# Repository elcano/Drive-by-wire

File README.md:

# DriveByWire

Obsolete. New code is in DBW version 5.

This repository is for use with the **Drive by Wire** board created to be used for the ELCANO self-driving tricycle. In order for this module to run external libraries are required.

Repositories were updated 6/8/2023 but clobbered previous history. Chief addition is use of an RC controller that allows manual control of throttle, brakes and steering.
The Sender files are intended for use on the Hi-Level board and do not really belong in the Drive-by-wire repository.

Libraries needed are listed below:

ALL Versions ________________________________
* PID by Brett Beauregard
    https://github.com/br3ttb/Arduino-PID-Library
    A simple controller calculator (proportional integral derivative) to calculate the error between a desired output and an actual output. Has files **PID_v1**

Version 3 (Arduino Mega) ________________________________
* CAN_BUS_SHIELD by Seeed-Studio
    https://github.com/Seeed-Studio/CAN_BUS_Shield
    Contains CAN_BUS communication protocols and required files such as **mcp_can** and **can-serial**

* Pin Change Interrupt by Nico Hood
    https://github.com/NicoHood/PinChangeInterrupt
    For custom configuration of Arduino pin properties. Has files **PinChangeInterupt**

* MCP48x2 DAC by Jonas Forsberg
    https://github.com/SweBarre/MCP48x2.
    Library for Digital to anolog converter. Has files **MCP48x2**

Version 4 (Arduino Due)  _______________________________________________
* Due CAN and CAN Common by Collin Kidder
    https://github.com/collin80/due_can
    https://github.com/collin80/can_common

## To Install

* Download the **Drive_By_Wire** module into the project parent directory
```
git clone https://github.com/elcano/Drive-by-wire.git
```
* Move into the **Drive_By_Wire** folder
```
cd Drive_By_Wire
```
* Download the required libraries
```
git clone https://github.com/Seeed-Studio/Seeed_Arduino_CAN.git
git clone https://github.com/br3ttb/Arduino-PID-Library.git
git clone https://github.com/NicoHood/PinChangeInterrupt.git
git clone https://github.com/SweBarre/MCP48x2.git
git clone https://github.com/ivanseidel/DueTimer.git
git clone https://github.com/collin80/can_common.git
git clone https://github.com/collin80/due_can.git
```
* Add the folders above to the IDE directory. In Windows, add the required libraries to: C:\Users\<username>\Documents\Arduino\libraries
* Arduino Due requires additional installation. On the IDE, go to Tools -> Boards -> Boards Manager -> Arduino SAM Boards (32-bits ARM Cortex-M3) 

## Navigating Arduino IDE: 
* **Selecting Board:** Tools -> Board -> Arduino AVR/SAM Boards -> Arduino Mega/Due
* **Selecting Serial Port:** Tools -> Port -> COM (Arduino Mega/Due)
* **Accessing Serial Monitor:** Right-hand Corner -> Select Baud Rate (115200)

## Drive-by-Wire: 
* **Low-level board code with RC control support with existing code for brakes, steering, and throttle.** 

## Test: 
* **Low-level board code with three functions to test each subsystems individually (brakes, steering, throttle).** 
* testBrake(): Activates brakes with 24V via Stop(), Holds brakes with 12V after 800ms via Update(), Releases brakes every ~2 seconds.
* testThrottle(): Gradually increases speed and decreases speed on DACA.
* testSteering(): Changes directions every 3 seconds, moving the linear actuator. 

## Sender: 
* **High-level board code to communicate with low-level board using CAN communication.** 
* Arguments for Function: Each data is reserved for 2 bytes. 
    *   currentSpeed: Controls the speed via the DACA, input: (0 -255).
    *   currentBrake: Apply and updates brakes if necessary, input: (0 - releases brakes, anything above 0 - applies brakes).
    *   currentAngle: Changes direction based on input (may need to calibrate based on sensors), left: 779 (1ms), middle: 722 (1.5ms), right: 639 (1.85ms).

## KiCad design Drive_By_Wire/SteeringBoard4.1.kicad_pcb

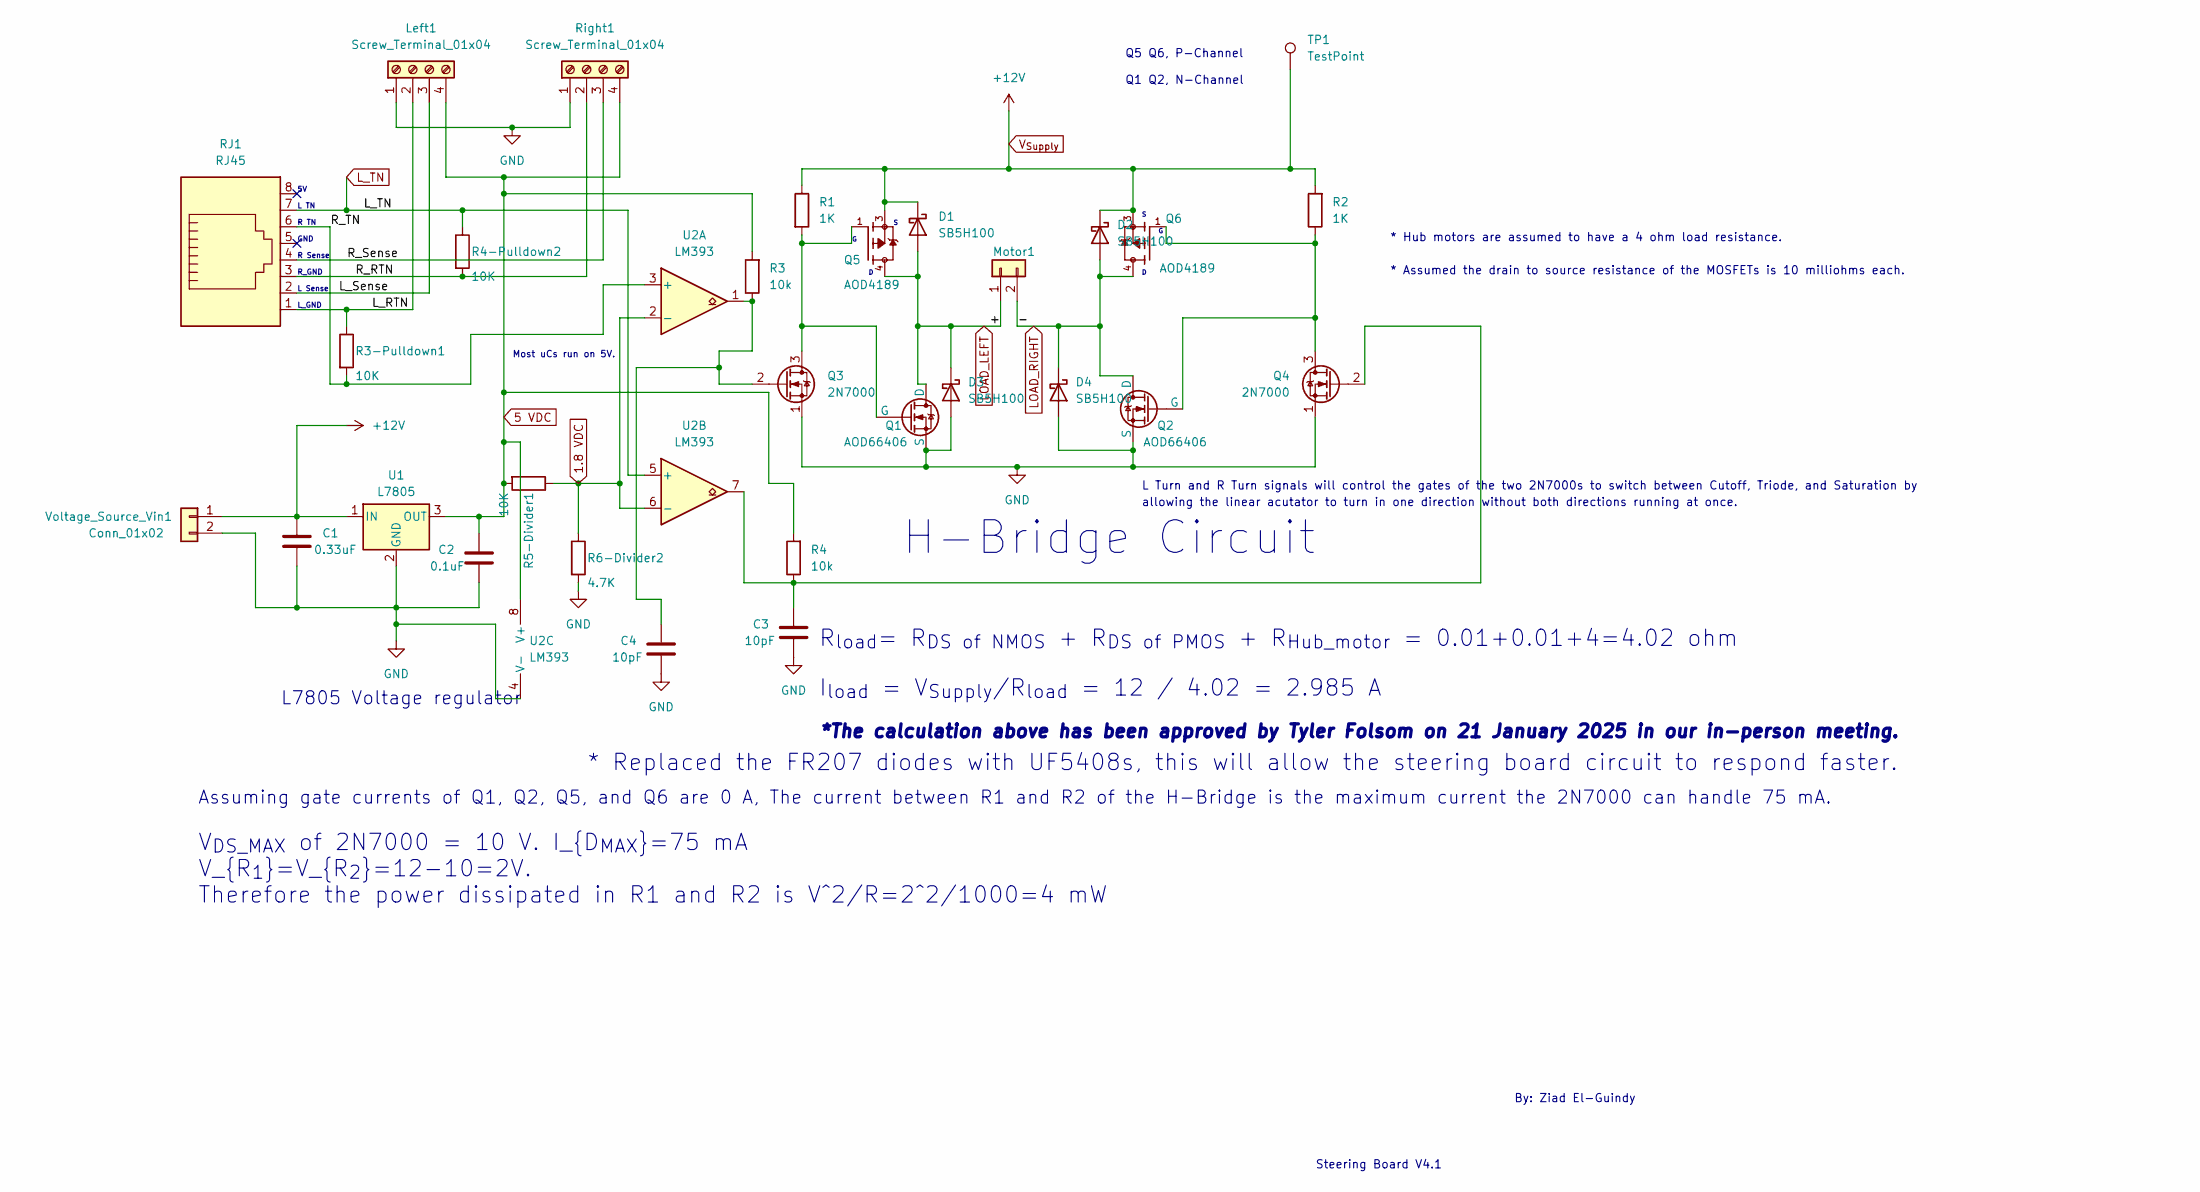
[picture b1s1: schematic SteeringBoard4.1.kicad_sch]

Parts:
C1: 0.33uF; C_Radial_D5.0mm_H7.0mm_P2.00mm
C2: 0.1uF; C_Radial_D5.0mm_H7.0mm_P2.00mm
C3, C4: 10pF; C_Radial_D5.0mm_H7.0mm_P2.00mm
D1, D2, D3, D4: SB5H100; D_DO-201AD_P15.24mm_Horizontal
Left1: Screw_Terminal_01x04; TerminalBlock_MetzConnect_Type059_RT06304HBWC_1x04_P3.50mm_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
Motor1: Conn_01x02; Anderson_Conn
Q1, Q2: AOD66406
Q3, Q4: 2N7000; TO-92_Inline
Q5, Q6: AOD4189; DPACK
R1, R2: 1K; R_Axial_DIN0414_L11.9mm_D4.5mm_P15.24mm_Horizontal
R3, R4: 10k; R_Axial_DIN0204_L3.6mm_D1.6mm_P5.08mm_Horizontal
R3-Pulldown1, R4-Pulldown2, R5-Divider1: 10K; R_Axial_DIN0204_L3.6mm_D1.6mm_P5.08mm_Horizontal
R6-Divider2: 4.7K; R_Axial_DIN0204_L3.6mm_D1.6mm_P5.08mm_Horizontal
RJ1: RJ45; RJ45_Amphenol_54602-x08_Horizontal
Right1: Screw_Terminal_01x04; TerminalBlock_MetzConnect_Type059_RT06304HBWC_1x04_P3.50mm_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
TP1: TestPoint; Pin_D1.0mm_L10.0mm
U1: L7805; TO-220-3_Vertical
U2: LM393; DIP-8_W7.62mm
Voltage_Source_Vin1: Conn_01x02; Anderson_Conn

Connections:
1.8 VDC: R5-Divider1.1, R6-Divider2.1, U2.2 (-), U2.6 (-)
5 VDC: C2.1, Left1.4, R3.2, R4.2, R5-Divider1.2, Right1.4, U1.3 (OUT), U2.8 (V+)
/L_RTN: Left1.2, R3-Pulldown1.1, RJ1.1
/L_Sense: Left1.3, RJ1.2
/R_RTN: R4-Pulldown2.2, RJ1.3, Right1.2
/R_Sense: RJ1.4, Right1.3
/R_TN: R3-Pulldown1.2, RJ1.6, U2.3 (+)
GND: C1.2, C2.2, C3.2, C4.2, D3.2 (A), D4.2 (A), Left1.1, Q1.3 (S), Q2.3 (S), Q3.1 (S), Q4.1 (S), R6-Divider2.2, Right1.1, U1.2 (GND), U2.4 (V-), Voltage_Source_Vin1.2
LOAD_LEFT: D1.2 (A), D3.1 (K), Motor1.1, Q1.1 (D), Q5.4
LOAD_RIGHT: D2.2 (A), D4.1 (K), Motor1.2, Q2.1 (D), Q6.4
L_TN: R4-Pulldown2.1, RJ1.7, U2.5 (+)
unnamed: Q1.2 (G), Q3.3 (D), Q5.1, R1.2
unnamed: Q2.2 (G), Q4.3 (D), Q6.1, R2.1
unnamed: C4.1, Q3.2 (G), R3.1, U2.1
unnamed: C3.1, Q4.2 (G), R4.1, U2.7
V_{Supply}: C1.1, D1.1 (K), D2.1 (K), Q5.3, Q6.3, R1.1, R2.2, TP1.1, U1.1 (IN), Voltage_Source_Vin1.1

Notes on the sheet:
R Sense
R TN
GND
V_{DS_MAX} of 2N7000 = 10 V. I_{D_{MAX}}=75 mA V_{R_{1}}=V_{R_{2}}=12-10=2V. Therefore the power dissipated in R1 and R2 is V^2/R=2^2/1000=4 mW
Steering Board V4.1
R_{load}= R_{DS of NMOS} + R_{DS of PMOS} + R_{Hub_motor} = 0.01+0.01+4=4.02 ohm
* Assumed the drain to source resistance of the MOSFETs is 10 milliohms each.
I_{load} = V_{Supply}/R_{load} = 12 / 4.02 = 2.985 A
Assuming gate currents of Q1, Q2, Q5, and Q6 are 0 A, The current between R1 and R2 of the H-Bridge is the maximum current the 2N7000 can handle 75 mA.
* Hub motors are assumed to have a 4 ohm load resistance.
* Replaced the FR207 diodes with UF5408s, this will allow the steering board circuit to respond faster.
allowing the linear acutator to turn in one direction without both directions running at once.
L TN
L Turn and R Turn signals will control the gates of the two 2N7000s to switch between Cutoff, Triode, and Saturation by
H-Bridge Circuit
Most uCs run on 5V.
*The calculation above has been approved by Tyler Folsom on 21 January 2025 in our in-person meeting.
L_GND
L Sense
Q5 Q6, P-Channel Q1 Q2, N-Channel
By: Ziad El-Guindy
R_GND
L7805 Voltage regulator

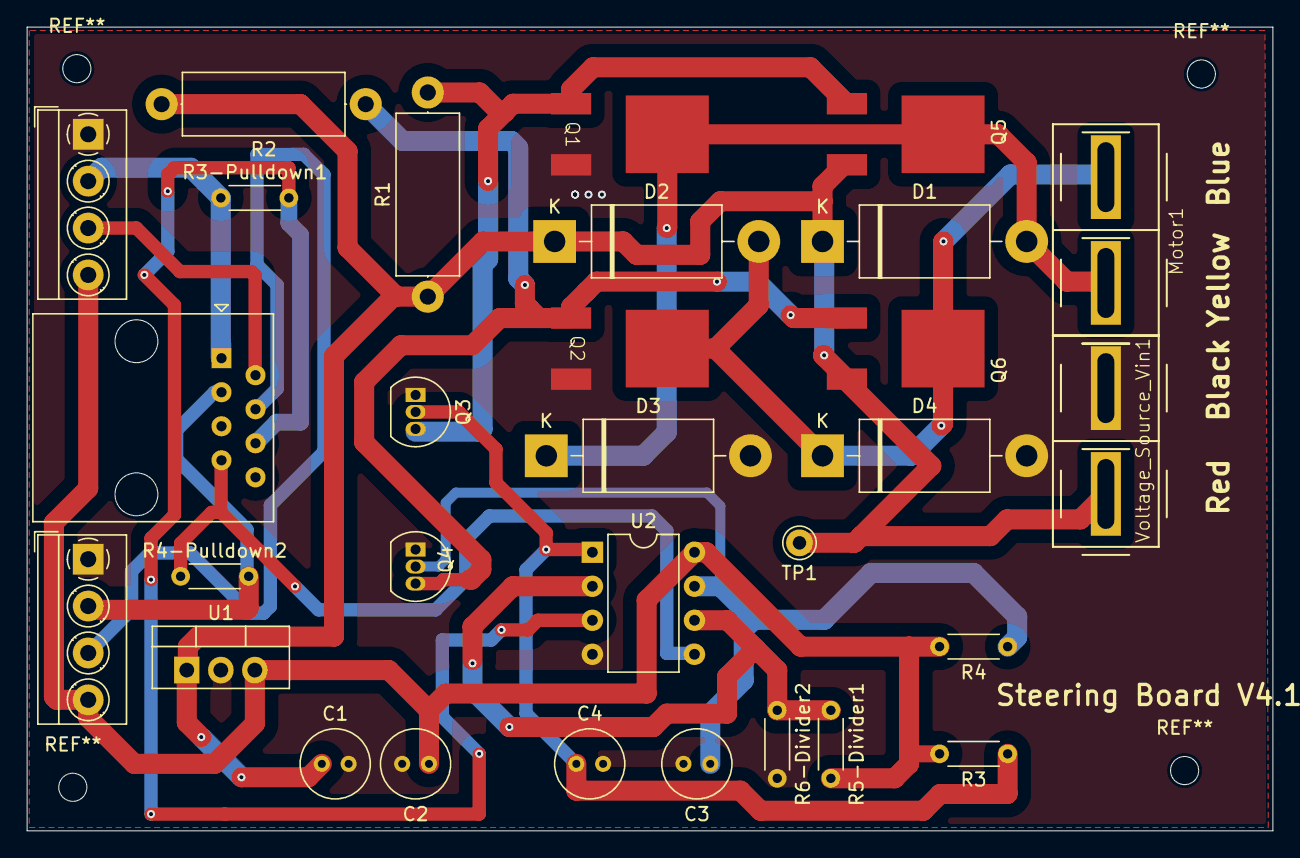
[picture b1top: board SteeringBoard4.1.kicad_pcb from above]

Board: 2 copper layers, 93.0 x 60.0 mm, 30 parts (0 on the bottom side), 16 nets.

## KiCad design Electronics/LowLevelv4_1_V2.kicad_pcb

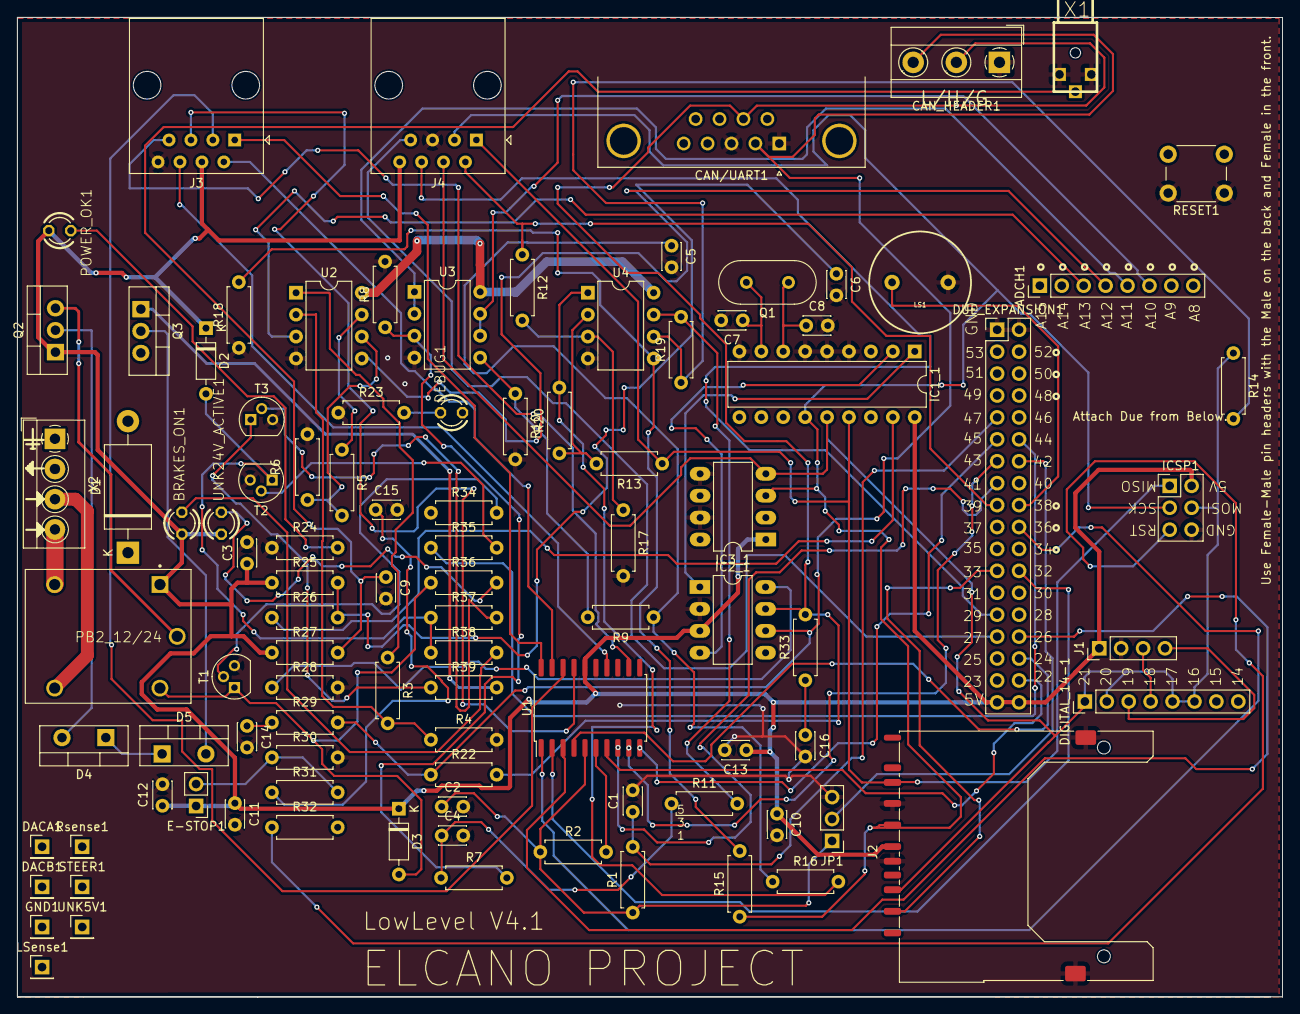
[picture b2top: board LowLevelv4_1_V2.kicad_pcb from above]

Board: 2 copper layers, 146.6 x 113.5 mm, 100 parts (0 on the bottom side), 80 nets.

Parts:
ADCH1: Analog In 8-11, DAC, CAN; PinHeader_1x08_P2.54mm_Vertical
BRAKES_ON1: LED3MM
C1, C9, C15: 1uF; C_Disc_D3.0mm_W2.0mm_P2.50mm
C2, C3, C4, C5, C6, C10, C11, C12, C13: 0.1uF; C_Disc_D3.0mm_W2.0mm_P2.50mm
C7, C8: 33pF; C_Disc_D3.0mm_W2.0mm_P2.50mm
C14, C16: 560pF; C_Disc_D3.0mm_W2.0mm_P2.50mm
CAN/UART1: DB9 Plug; DSUB-9_Male_Horizontal_P2.77x2.84mm_EdgePinOffset4.94mm_Hou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
CAN_HEADER1: CONN_03-SCREW-5MM; TerminalBlock_MetzConnect_Type055_RT01503HDWU_1x03_P5.00mm_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
D1: 1N5400; D_DO-201_P15.24mm_Horizontal
D2, D3: 1N4148; D_DO-35_SOD27_P7.62mm_Horizontal
D4, D5: MBR745; TO-220-2_Vertical
DACA1: PTR1PAD1-17; PinHeader_1x01_P2.54mm_Vertical
DACB1: PTR1PAD1-17; PinHeader_1x01_P2.54mm_Vertical
DEBUG1: LED3MM
DIGITAL_14-1: Digital 14-21; PinHeader_1x08_P2.54mm_Vertical
DUE_EXPANSION1: Digital 22-53; PinHeader_2x18_P2.54mm_Vertical
E-STOP1: PINHD-1X2; PinHeader_1x02_P2.54mm_Vertical
GND1: PTR1PAD1-17; PinHeader_1x01_P2.54mm_Vertical
IC1_1: MCP2515(MCP2510)P; DIP-18_W7.62mm
IC2_1: MCP2551DIL08; DIP-8_W7.62mm_LongPads
IC3_1: MCP4802; DIP-8_W7.62mm_LongPads
ICSP1: 2x3; PinHeader_2x03_P2.54mm_Vertical
J1: ROS_CONN; PinHeader_1x04_P2.54mm_Vertical
J2: SD_Card; SD_Kyocera_145638109511859+
J3: RJ45_MOTOR; RJ45_Amphenol_54602-x08_Horizontal
J4: RJ45_STEER; RJ45_Amphenol_54602-x08_Horizontal
JP1: Jumper_3_Open; PinHeader_1x03_P2.54mm_Vertical
LS1: BUZZER-PTH; BUZZER-12MM
LSense1: PTR1PAD1-17; PinHeader_1x01_P2.54mm_Vertical
PB2_12/24: ORWH-SH-105D1F,000; TE_ORWH-SH-105D1F,000
POWER_OK1: LED3MM
Q1: ECS-160-20-46X; Crystal_HC49-U_Vertical
Q2, Q3: IRLZ44N; TO-220-3_Vertical
R1, R11, R16: 4.7k; R_Axial_DIN0207_L6.3mm_D2.5mm_P7.62mm_Horizontal
R2, R4, R8, R30, R31: 10k; R_Axial_DIN0207_L6.3mm_D2.5mm_P7.62mm_Horizontal
R3, R5, R6, R7, R9, R10: 5.15k; R_Axial_DIN0207_L6.3mm_D2.5mm_P7.62mm_Horizontal
R12, R13, R14, R15, R17, R18, R19, R20: 22k; R_Axial_DIN0207_L6.3mm_D2.5mm_P7.62mm_Horizontal
R22: 120; R_Axial_DIN0207_L6.3mm_D2.5mm_P7.62mm_Horizontal
R23, R24, R26, R34, R35, R36, R38: 1K; R_Axial_DIN0207_L6.3mm_D2.5mm_P7.62mm_Horizontal
R25: 20K; R_Axial_DIN0207_L6.3mm_D2.5mm_P7.62mm_Horizontal
R27, R28: 4.7K; R_Axial_DIN0207_L6.3mm_D2.5mm_P7.62mm_Horizontal
R29, R33, R39: 100; R_Axial_DIN0207_L6.3mm_D2.5mm_P7.62mm_Horizontal
R32: 0; R_Axial_DIN0207_L6.3mm_D2.5mm_P7.62mm_Horizontal
R37: 1k; R_Axial_DIN0207_L6.3mm_D2.5mm_P7.62mm_Horizontal
RESET1: MOMENTARY-SWITCH-SPST-PTH-6.0MM; SW_PUSH_6mm
Rsense1: PTR1PAD1-17; PinHeader_1x01_P2.54mm_Vertical
STEER1: PTR1PAD1-17; PinHeader_1x01_P2.54mm_Vertical
T1, T2, T3: 2N3904; TO-92
U1: TXB0108DQSR; SOIC-20W_7.5x12.8mm_P1.27mm
U2, U3, U4: LM358; DIP-8_W7.62mm
UNK5V1: PTR1PAD1-17; PinHeader_1x01_P2.54mm_Vertical
UNK24V_ACTIVE1: LED3MM
X1: ODO_JACK
X2: TerminalBlock_4Ucon_1x04_P3.50mm_Horizontal

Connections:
+3.3V: C2.1, JP1.1 (A), R1.1, R2.1, U1.5 (VCCA)
+5V: BRAKES_ON1.A, C3.1, C10.1, C11.1, C12.1, C13.1, D2.1 (K), D3.1 (K), DUE_EXPANSION1.35, DUE_EXPANSION1.36, E-STOP1.1, IC1_1.18 (VDD), IC2_1.3 (VDD), IC3_1.1, ICSP1.2, J1.1 (5V), J2.4 (VDD), J3.4, J4.8, PB2_12/24.1 (C1), POWER_OK1.A, Q2.1 (G), R25.1, R27.1, U1.16 (VCCB), UNK24V_ACTIVE1.A
+12V: U2.8 (V+), U3.8 (V+), U4.8 (V+)
/Low Level 4.1 Segment 1/5V_DAC1: R3.1, U2.1
/Low Level 4.1 Segment 1/5V_FWDSW: J3.1, U1.20 (B1)
/Low Level 4.1 Segment 1/5V_REGEN: J3.6, U1.14 (B5)
/Low Level 4.1 Segment 1/5V_REVERSE: J3.5, U1.17 (B4)
/Low Level 4.1 Segment 1/5V_SPEEDOMETER: J3.7, U1.12 (B7)
/Low Level 4.1 Segment 1/5V_STEER_PULSE: J3.3, U1.18 (B3)
/Low Level 4.1 Segment 1/5V_THROTTLE: R5.1, U2.7
/Low Level 4.1 Segment 1/5V_WATCHDOG: J3.2, U1.19 (B2)
/Low Level 4.1 Segment 1/BRAKE_PULSE: DUE_EXPANSION1.15, U1.8 (A6)
/Low Level 4.1 Segment 1/CAN_ENABLE: DUE_EXPANSION1.14, JP1.2 (C)
/Low Level 4.1 Segment 1/CHIP_SELECT_ANGLE: DUE_EXPANSION1.17, J4.2, R12.1
/Low Level 4.1 Segment 1/CHIP_SELECT_SD: DUE_EXPANSION1.23, J2.1 (CD/DAT3)
/Low Level 4.1 Segment 1/DAC1: ADCH1.3, U2.3 (+)
/Low Level 4.1 Segment 1/EBIKE_POWER_IN: DUE_EXPANSION1.11, U1.10 (A8)
/Low Level 4.1 Segment 1/FWDSW: DUE_EXPANSION1.20, U1.1 (A1)
/Low Level 4.1 Segment 1/IRPT_WHEEL: C1.1, DUE_EXPANSION1.9, R1.2
/Low Level 4.1 Segment 1/REGEN: DUE_EXPANSION1.34, U1.7 (A5)
/Low Level 4.1 Segment 1/REVERSE: DUE_EXPANSION1.32, U1.4 (A4)
/Low Level 4.1 Segment 1/RX1_DBW: DIGITAL_14-1.3, J1.4 (RX1)
/Low Level 4.1 Segment 1/R_SENSE: ADCH1.5, U3.1, U3.2 (-)
/Low Level 4.1 Segment 1/SPEEDOMETER: DUE_EXPANSION1.13, U1.9 (A7)
/Low Level 4.1 Segment 1/STEER_PULSE/L_TURN: DUE_EXPANSION1.30, U1.3 (A3)
/Low Level 4.1 Segment 1/THROTTLE_DAC0: ADCH1.4, U2.5 (+)
/Low Level 4.1 Segment 1/TX1_DBW: DIGITAL_14-1.4, J1.3 (TX1)
/Low Level 4.1 Segment 1/WATCHDOG: DUE_EXPANSION1.24, U1.2 (A2)
/Low Level 4.1 Segment 2/CAN_RXD: IC1_1.2 (RXCAN), IC2_1.4 (RXD)
/Low Level 4.1 Segment 2/CAN_TXD: IC1_1.1 (TXCAN), IC2_1.1 (TXD)
/Low Level 4.1 Segment 2/OSC1: C7.1, IC1_1.8 (OSC1), Q1.2
/Low Level 4.1 Segment 2/OSC2: C8.1, IC1_1.7 (OSC2), Q1.1
/Low Level 4.1 Segment 2/RS: IC1_1.17 (RESET), R26.1
/Low Level 4.1 Segment 3/SOLENOID_OUT: D4.1 (K), D5.1 (K)
/Low Level 4.1 Segment 3/SOLENOID_POWER: PB2_12/24.3 (C), Q2.3 (S)
BRAKE_ON: DUE_EXPANSION1.12, R35.1
BUZZER: DUE_EXPANSION1.18, LS1.+ (1)
CANH: CAN/UART1.7, CAN_HEADER1.2, IC2_1.7 (CANH), R22.2, R33.2
CANL: CAN/UART1.2, CAN_HEADER1.3, IC2_1.6 (CANL), R22.1, R29.2
ESTOP_INT: C15.1, R31.1
GND: C1.2, C2.2, C3.2, C4.2, C5.2, C6.2, C7.2, C8.2, C9.2, C10.2, C11.2, C12.2, C13.2, C14.2, C15.2, C16.2, CAN/UART1.1, CAN/UART1.3, CAN_HEADER1.1, DUE_EXPANSION1.1, DUE_EXPANSION1.2, IC1_1.4 (TX0RTS), IC1_1.5 (TX1RTS), IC1_1.6 (TX2RTS), IC1_1.9 (VSS), IC2_1.2 (VSS), IC3_1.5, IC3_1.7, ICSP1.6, J1.2 (GND), J2.3 (VSS), J2.6 (VSS), J2.12 (SHELL1), J2.13 (SHELL2), J3.8, J4.5, JP1.3 (B), LS1.- (2), R4.2, R6.2, R8.2, R10.2, R17.2, R18.1, R23.1, R24.1, R28.2, R30.2, RESET1.1, T1.3 (E), T2.3 (E), T3.3 (E), U1.15 (GND), U2.4 (V-), U3.4 (V-), U4.4 (V-), X1.P$2 (2), X1.P$3 (3)
L_SENSE: ADCH1.6, U3.6 (-), U3.7
L_TN: DUE_EXPANSION1.29, J4.7
MISO: IC1_1.15 (SO), ICSP1.1, J2.7 (DAT0), J4.1, R13.1
MOSI: DIGITAL_14-1.1, DIGITAL_14-1.2, DIGITAL_14-1.5, DIGITAL_14-1.6, IC1_1.14 (SI), IC3_1.4, ICSP1.4, J2.2 (CMD), J4.4, R14.1
unnamed: BRAKES_ON1.K (C), R38.2
unnamed: C4.1, R7.1, R11.1
unnamed: C5.1, R9.1, R16.1
unnamed: C6.1, R25.2, R26.2
unnamed: C14.1, R29.1
unnamed: C16.1, R33.1
unnamed: D2.2 (A), R37.1, R38.1, T2.1 (C)
unnamed: D3.2 (A), PB2_12/24.2 (C2), R36.1, T1.1 (C)
unnamed: D4.2 (A), Q2.2 (D)
unnamed: D5.2 (A), Q3.2 (D)
unnamed: DEBUG1.K (C), R23.2
unnamed: E-STOP1.2, R30.1, R31.2
unnamed: IC2_1.8 (RS), R28.1
unnamed: POWER_OK1.K (C), R24.2
unnamed: Q3.1 (G), R39.2
unnamed: R11.2, R19.2, U4.7
unnamed: R16.2, R20.2, U4.1
unnamed: R34.2, T1.2 (B)
unnamed: R35.2, T2.2 (B)
unnamed: R37.2, T3.2 (B)
unnamed: R39.1, T3.1 (C)
unnamed: R2.2, U1.6 (OE)
unnamed: R3.2, R4.1, U2.2 (-)
unnamed: R5.2, R6.1, U2.6 (-)
unnamed: R7.2, R8.1, U3.3 (+)
unnamed: R9.2, R10.1, U3.5 (+)
unnamed: R12.2, R17.1, U4.3 (+)
unnamed: R13.2, R20.1, U4.2 (-)
unnamed: R15.2, R18.2, U4.5 (+)
unnamed: R14.2, R19.1, U4.6 (-)
unnamed: R36.2, UNK24V_ACTIVE1.K (C)
RESET: ICSP1.5, R32.1
R_TN: DUE_EXPANSION1.27, J4.6
SCK: IC1_1.13 (SCK), IC3_1.3, ICSP1.3, J2.5 (CLK), J4.3, R15.1
WHEELROTATION: C9.1, R27.2, X1.P$1 (1)

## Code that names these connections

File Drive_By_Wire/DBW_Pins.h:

#ifndef _DBW_PINS_
#define _DBW_PINS_

#define DEBUG false
#define USE_PIDS false // throttle currently uses a PID controller, Steering does not current use a PID controller

#include <Arduino.h>

//Version can be 1,3 or 4; LLB = Low Level Board = Drive By Wire
#define DBWversion 4

/*---------- Version 1 - No Longer supported------------------------
#if DBWversion == 1
//Wheel click interrupt
#define IRPT_WHEEL         3
#define STEER_OUT_PIN      5
#define STEER_ON           8
#define BrakeVoltPin       9
#define BrakeOnPin        10
#define SelectAB          53
#define SelectCD          49
#define DAC_CHANNEL        0
#define AngleSensorLeft   A2
#define AngleSensorRight  A3
*/
/*---------- Version 3: Arduino Mega -------------------------------------*/
#if DBWversion < 4

/* Pin declarations */
// Serial Monitor uses pins 0,1 for RX0,TX0
// Servo to control the brakes; not used

#define BRAKE_PULSE_PIN     2
 // keep-alive watchdog is not yet implemented
#define WATCHDOG_PIN        5  
// Pin used to steer the vehicle with a pulse
#define STEER_PULSE_PIN     6
// Relay that turns on power to the steering system
#define STEER_ON_PIN        8
// Wheel angle sensors mounted on left and right steering columns
#define L_SENSE_PIN    A2
#define R_SENSE_PIN    A3

// Command to e-bike controller to use regenerative braking; not used 
#define REGEN_PIN          22
// Command to e-bike controller to drive in reverse; not used
#define REVERSE_PIN        24
// Switch to drive in forward or reverse; not used
#define FWDSW_PIN          34
#define D_36_PIN           36  // Not used
// Brakes, have relays for both on/off as well as selecting 12/24v power.
#define BrakeVoltPin       37
#define BUZZER_PIN         38  // Not used
#define BrakeOnPin         39

// CANbus slave select
#define CAN_SS_PIN         49  
// SPI chip select for DAC slave select. Channel A is for throttle
#define DAC_SS_PIN         48 
// we only use channel A for the throttle. B is routed but unused.
#define DAC_CHANNEL         0   
// Pins 51,52,53 are MISO, MOSI, SCK.
// originally intended as a return ground, these analog pins are free and on the steering header.
// Intent was to use L_SENSE - L_RTN as a differential signal.
//#define L_RTN_PIN        A6
//#define R_RTN_PIN        A7

/* Signals A8 through A15 are digital interrupts */
/* The Arduino Mega only has 6 interrupts, but an additional 8 can be added through the port pin change interrupt. */
//Wheel click interrupt (digitally high or low, referred to as an "odometer"). Once per wheel revolution.
// IRPT_WHEEL = WHEELROTATION
#define IRPT_WHEEL         A8
// physical E-Stop port; not used
#define IRPT_ESTOP_PIN     A9 
// Interrupt for can msg; not used
#define IRPT_CAN_PIN       A10 

// motor hall phases occur multiple times per wheel revolution
// A future design may make use of these for more precise speed feedback.
// The speedometer_pin would be jumpered to the signal in use
//Not implemented
#define SPEEDOMETER_PIN    A11
#define IRPT_PHASE_C       A12
#define EBIKE_POWER_IN_PIN A13
#define IRPT_PHASE_B       A14
#define IRPT_PHASE_A       A15


/*---------- Version 4: Arduino Due -------------------------------------*/
#else // DBWversion >=4

// Serial Monitor uses pins 0,1 for RX0,TX0
// Pins D0-D13 and A0-A5 are reserved for the Motor Shield
// The shield may block access to A6 and A7.
/*
 *  --------Motor shield pins --------------
 *  Channel A Current sensing   A0
 *  Channel B Current sensing   A1
 *  In2 Connector               A2
 *  In3 Connector               A3
 *  Channel A Speed (PWM)       3
 *  Out5 connector              5
 *  Out6 connector              6
 *  Channel B Brake             8
 *  Channel A Brake             9
 *  Channel B Speed (PWM)       11
 *  Channel A Direection        12
 *  Channel B Direection        13
 *  
 *  Version 4 connectors:
 *  RJ45 Steering: 
 *        L_RTN, L_SENSE, GND, 5V, STEER_PULSE, GND, R_RTN, R_SENSE, GND, 5V
 *  Two 4 wire screw terminals for CAN bus
 *        12V in, GND, CAN LO, CAN HI
 *  One 4 wire screw terminal for brake solenoid
 *        12V in, GND, 24V in, Brake solenoid out (12 or 24V)
 *        The 12V in on this connector is tied to the 12V in on the CAN bus connector,
 *        There should be only one connector to 12V power in, 
 *        A spare 12V connector could be wired to the motor shield, which
 *        already has a common ground.`
 *  One 4 wire screw terminal:
 *        12V out (controlled by STEER_ON), GND, IRPT_WHEEL, GND
 *  RJ45 to e-bike Motor Controller:
 *        FWDSW, EBIKE_POWER_IN, GND, DAC0, DAC1, SPEEDOMETER, WATCHDOG, 
 *        BRAKE_PULSE, REVERSE, REGEN, 

 */

// Wheel angles sensors mounted on left and right steering columns
#define L_SENSE_PIN        A10
#define R_SENSE_PIN        A11
// originally intended as a return ground, these analog pins are free and on the steering header.
// Intent was to use L_SENSE - L_RTN as a differential signal.
//#define L_RTN_PIN          26
//#define R_RTN_PIN          27

//----NEWLY ADDED PINs 6/8/25-----
#define THROTTLE_BR_CH2_PIN 9
#define STEERING_CH1_PIN 8

#define DRIVE_MODE_CH4_PIN 11
#define RC_CH3_ESTOP 10
#define RIGHT_TURN_PIN 29
#define LEFT_TURN_PIN 27

// Command to e-bike controller to use regenerative braking; not used 
#define REGEN_PIN           22
// The odd numbered pins from 23 to 39 are unassigned.

// Command to e-bike controller to drive in reverse; not used
#define REVERSE_PIN         24
// Pin used to steer the vehicle with a pulse
#define STEER_PULSE_PIN     26
// Relay that turns on power to the steering system
#define STEER_ON_PIN        4
// Debug or status for DBW
#define DBW_LED             30
 // keep-alive watchdog is not yet implemented
#define WATCHDOG_PIN        32  
// Pins 34 and 35 could conflict with the Router board on the Bridge.
// Switch to drive in forward or reverse; not used
#define FWDSW_PIN          36
#define BUZZER_PIN         38  // Not used
#define BrakeOnPin         39
// Brakes, have relays for both on/off as well as selecting 12/24v power.
#define BrakeVoltPin       40

// Servo to control the brakes; not used
#define BRAKE_PULSE_PIN    41
/* Signals D42-49 are digital interrupts */
/* If implemented on aa Arduino Mega, these are on Port L and can use pin change interrupt. */
/* Any Arduino Due pin can be an interrupt. */
// Interrupt for can msg; not used
#define IRPT_CAN_PIN       42
// Multiple clicks per wheel revolution (not implemented)
#define SPEEDOMETER_PIN    43
// When the E-bike controller has power, this line is 5V.
// If it falls to zero, ebike has lost power.
#define EBIKE_POWER_IN_PIN 45

// Wheel click interrupt (digitally high or low, referred to as an "odometer"). Once per wheel revolution.
// Odometer reed switch is pulled up to high voltage.
// IRPT_WHEEL = WHEELROTATION
#define IRPT_WHEEL         47
// DAC channel is he DAC address for throttle; not an Arduino pin.
#define DAC_CHANNEL         0   
/*------------ Dropped signals ------------------
 * The following signals have been dropped
// Motor hall phases occur multiple times per wheel revolution
// A future design may make use of these for more precise speed feedback.
// The speedometer_pin would be jumpered to the signal in use
   The three Hall Phases were never used: IRPT_PHASE_A, IRPT_PHASE_B, IRPT_PHASE_C
   If we use a signal from the hub motor, it will be on the SPEEDOMETER_PIN 

// physical E-Stop port; not used
  IRPT_ESTOP_PIN is not used. It was intended for a remote e-stop, but the
  e-stop now comes from the CAN bus.
  D_36_PIN    // Never used; intended as a spare signal
 -------------------------------------------------------------*/

// On the Due, SPI, CAN_SS and DAC_SS are not used. Use DAC0, DAC1, CANRX and CANTX  
// On Due MISO, MOSI, SCK are only on the ICSP, which is blocked by the motor shield.

#endif  // DBWversion 

#endif   //_DBW_PINS_

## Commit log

2019-12-04 Rename Elcano_C2_LowLevel_TimedBrakes.ino to TimedBrakes.ino
2019-12-04 Rename Elcano_C2_LowLevel.ino to Drive_ByWire.ino
2019-12-04 Rename Drive_ByWire.ino to Drive_By_Wire.ino
2020-04-24 just a test comment
2020-04-24 comment
2020-05-12 Moving library files to compile --> TODO: Consolidate libraries after linking HL/LL/RTR Arduino systems back together
2020-05-12 Updating readme to include needed libraries
2020-05-22 Fixed #include in vehicle.cpp so the sketch will compile
2020-05-31 CAN Message update
    Corrected CAN message parsing
    Corrected angle mapping for CAN message.
2020-08-01 Added DBW_Pins.h
2020-08-03 added Version 4 signals to DBW_Pins.h
2020-08-14 Updated V4 pin numbers; changes for Due
2020-10-31 convert mcp_can methods to due_can / can_common
2020-10-31 Add due conversion for sending CAN messages
2020-10-31 Update code to remove TODO comments and clean up Due conversion code
2020-10-31 Add preprocessor command to mega library
2020-11-20 Clean up comments on vehicle.h
2021-05-25 Updated install instructions for Drive_By_Wire module
2023-03-07 add modified files and updated README.md
2023-06-08 First half 2023 changes
2023-07-01 Update and rename Settings.h to SettingsTemplate.h
    Download SettingsTemplate.h, and save it as your own Settings.h. Settings.h does not belong in the repository.
2023-07-01 Settings.h replaced by SettingsTemplate.h and comments added
2023-07-01 Settings.h replaced by SettingsTemplate.h
    Comments added. Redundant includes dropped from vehicles.cpp. Added gitignore
2023-07-01 Removed code from Settings.h
    Get the real stuff from SettingsTemplate.h
2023-07-03 Removed undocumented TESTING
    Renamed LLBversion to DBWversion; set USE_PIDS true
2023-07-03 DBWversion checks Mega/Due
2023-07-05 Documented needed libraries
2023-07-05 Removed unneeded CAN files
    #include can*.h not used.
2024-04-15 New steering and data logging for steering
2024-04-20 Add files via upload
    Using left angle sensor instead of right angle sensor RC commands currently work.
2024-05-20 Datalogger and Steering Software Implemented
    PID controller is not used for Steering or throttle and CAN bus is disabled due to problem with board.
2024-06-24 Add files via upload
    Changed steering, throttle, brake, and RC controller to non static to fix the compilation error when using the Arduino Due
2024-07-11 GPS addition
    For the future version we are going to remove the GPS functionality and replace the current shield with a new logging shield that can interface with the Arduino due.
2024-07-12 Throttle produces correct outputs
2024-07-17 Brakes and Throttle verified
    Inverter option in brake.cpp set to true and throttle is set initially to max to get the wheel moving
2024-07-31 Data logger verified and takes the compile time if more recent
2025-03-15 Add files via upload
    This is the updated steering board for the Elcano Drive-by-wire system.
2025-03-17 added controlHBridge function
2025-06-08 Testing Changes
    Includes logging, brakes, throttle, etc
2025-06-09 Create CAN_Receiver
    This receiver code is used to test the Arduino DUE's ability to receive CAN messages using a transceiver. By default, this code sets a digital pin to high as a high-level confirmation that the CAN si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
2025-06-09 LowLevel V4.1 PCB Diagram KiCAD + Steering Board.
    These are all the KiCAD, EasyEDA, and LTspice files that our team has modified for DBW V4.1.
2025-06-09 changes
    changes
2025-06-09 Updated Changes (6/9/2025)
    Minor fixes
2025-06-09 changes now
    updates to brakes and vehicle
2025-06-09 Updated DBW V4.1 Pin mapping for LowLevel V4.1
    D27 is L_TN and D_29 is R_TN to better fit the operation of the dual steering signal Steering Board V4.1.
    Make any changes to any other signals when necessary. Leave R_TN and L_TN as is.
2025-06-09 3:30pm changes 6/9/25
    3:30pm changes 6/9/25
2025-06-11 Datalogger outputs of DBW V4.1 code.
    This ZIP archive contains LOG00-LOG21.csv.
2025-08-19 Create JetsonNano_Autonomous_DBW
    Python Algorithm for Autonomous Test Bench, includes speed sensor, GPS speed, waypoint input, CAN outputs
2026-05-07 README.md indicates DBW versions 1-4 is obsolete
